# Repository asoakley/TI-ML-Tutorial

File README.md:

# TI-ML-Tutorial
<html>
<body>
<h1>TI Machine Learning Robotics</h1>
<h3>Tutorial repository for TI-RSLK MAX Machine Learning used for NC State ECE Senior Design Fall 2021-Spring 2022</h3>
<ul>
    <li>PCB folder contains Eagle CAD files for the custom PCB schematic file as well as the board file. It also includes the necessary gerbers and libraries needed to recreate the custom sensors PCB</li>
    <ul>
        <li>Eagle Libraries contains the libraries needed to recreate our schematic and board</li>
        <li>PCB Gerbers are the gerber files that can be sent to a manufacturer for printing</li>
    </ul>
    <li>libraries folder contains the libraries used in Arduino IDE to get the MSP432 microcontroller and the RSLK MAX to function. 
    It also contains two pretrained Edge Impulse libraries that we have tested for both Terrrain Recognition and Keyword Recognition</li>
    <li>prediction folder contains the Arduino code for running edge impulse models. 
    It contains code for both Audio and Accelerometer Machine Learning as well as a template code for any sensors you would like to have.</li>
    <li>test and training folder contains Arduino code to sample accelerometer and/or audio data of the RSLK MAX</li>
</ul>
    
<p> Check out our Hackster.io pages for
<a href="https://www.hackster.io/nc-state-ece-design-team-3-fall-2021-spring-2022/ti-rslk-machine-learning-robotics-terrain-recognition-a90367">Terrain Recognition</a> and 
<a href="https://www.hackster.io/nc-state-ece-design-team-3-fall-2021-spring-2022/ti-rslk-machine-learning-robotics-keyword-recognition-d96755">Keyword Recognition</a>!
</p>
</body>
</html>

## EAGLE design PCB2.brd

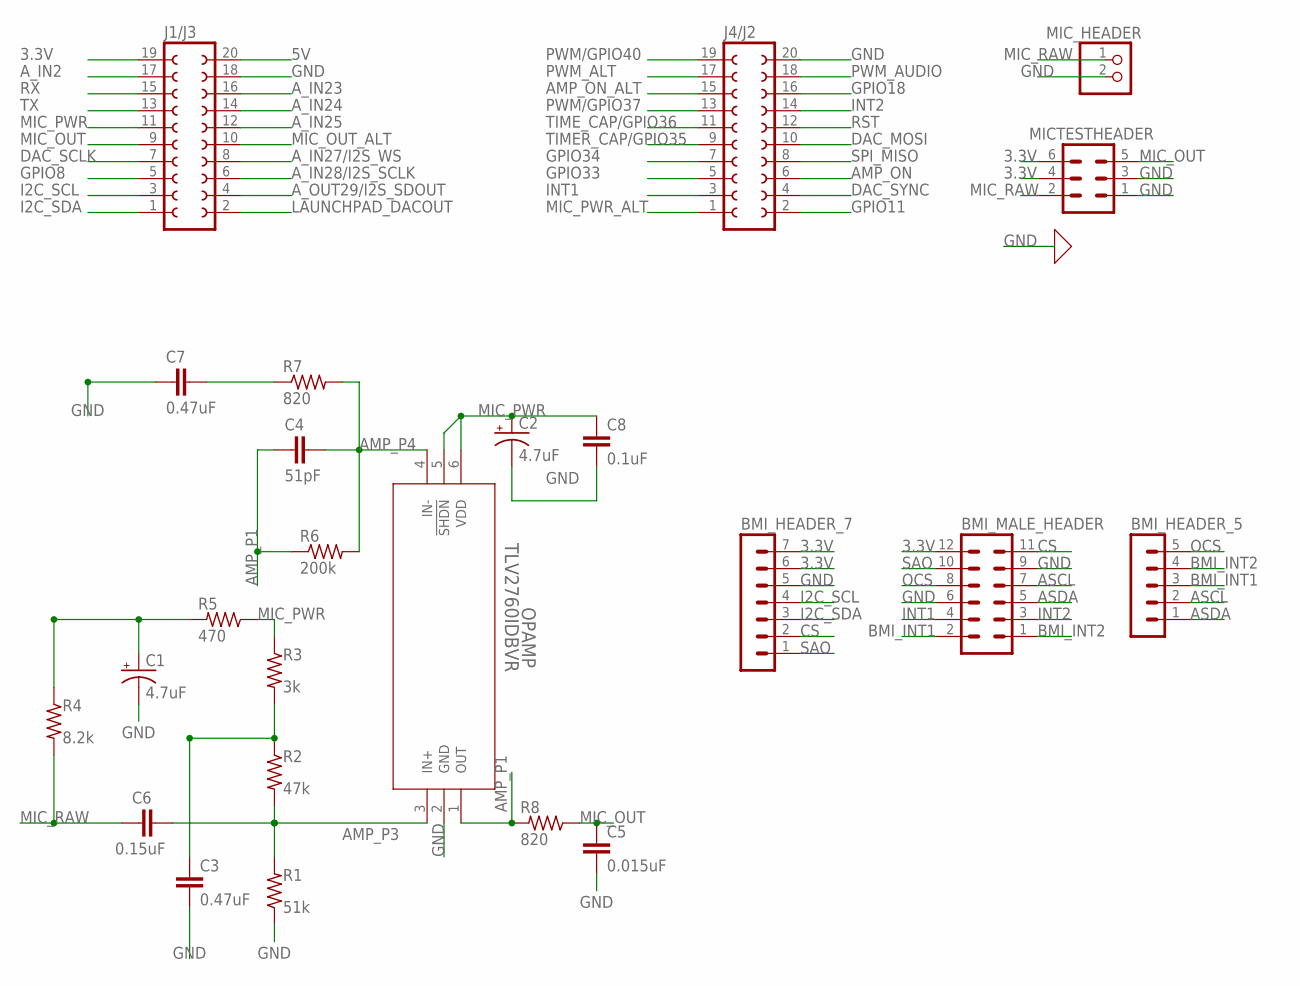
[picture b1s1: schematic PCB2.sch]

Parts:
BMI_HEADER_5: MA05-1
BMI_HEADER_7: MA07-1
BMI_MALE_HEADER: MA06-2
C1, C2: 4.7uF; B/3528-21W
C3, C7: 0.47uF; C0603
C4: 51pF; C0603
C5: 0.015uF; C0603
C6: 0.15uF; C0603
C8: 0.1uF; C0603
J1/J3, J4/J2: FE10-2W
MICTESTHEADER: MA03-2
MIC_HEADER: PINHD-1X2; 1X02
OPAMP: TLV2760IDBVR; DBV6
R1: 51k; MINI_MELF-0204R
R2: 47k; MINI_MELF-0204R
R3: 3k; MINI_MELF-0204R
R4: 8.2k; MINI_MELF-0204R
R5: 470; MINI_MELF-0204R
R6: 200k; MINI_MELF-0204R
R7, R8: 820; MINI_MELF-0204R

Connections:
3.3V: BMI_HEADER_7.6, BMI_HEADER_7.7, BMI_MALE_HEADER.12, J1/J3.19, MICTESTHEADER.4, MICTESTHEADER.6
5V: J1/J3.20
AMP_ON: J4/J2.6
AMP_ON_ALT: J4/J2.15
AMP_P1: C4.2, OPAMP.1 (OUT), R6.1, R8.2
AMP_P3: C6.2, OPAMP.3 (IN+), R1.2, R2.2
AMP_P4: C4.1, OPAMP.4 (IN-), R6.2, R7.2
ASCL: BMI_HEADER_5.2, BMI_MALE_HEADER.7
ASDA: BMI_HEADER_5.1, BMI_MALE_HEADER.5
A_IN2: J1/J3.17
A_IN23: J1/J3.16
A_IN24: J1/J3.14
A_IN25: J1/J3.12
A_IN27/I2S_WS: J1/J3.8
A_IN28/I2S_SCLK: J1/J3.6
A_OUT29/I2S_SDOUT: J1/J3.4
BMI_INT1: BMI_HEADER_5.3, BMI_MALE_HEADER.2
BMI_INT2: BMI_HEADER_5.4, BMI_MALE_HEADER.1
CS: BMI_HEADER_7.2, BMI_MALE_HEADER.11
DAC_MOSI: J4/J2.10
DAC_SCLK: J1/J3.7
DAC_SYNC: J4/J2.4
GND: BMI_HEADER_7.5, BMI_MALE_HEADER.6, BMI_MALE_HEADER.9, C1.-, C2.-, C3.2, C5.2, C7.2, C8.2, J1/J3.18, J4/J2.20, MICTESTHEADER.1, MICTESTHEADER.3, MIC_HEADER.2, OPAMP.2 (GND), R1.1
GPIO8: J1/J3.5
GPIO11: J4/J2.2
GPIO18: J4/J2.16
GPIO33: J4/J2.5
GPIO34: J4/J2.7
I2C_SCL: BMI_HEADER_7.4, J1/J3.3
I2C_SDA: BMI_HEADER_7.3, J1/J3.1
INT1: BMI_MALE_HEADER.4, J4/J2.3
INT2: BMI_MALE_HEADER.3, J4/J2.14
LAUNCHPAD_DACOUT: J1/J3.2
MIC_OUT: C5.1, J1/J3.9, MICTESTHEADER.5, R8.1
MIC_OUT_ALT: J1/J3.10
MIC_PWR: C2.+, C8.1, J1/J3.11, OPAMP.5 (!SHDN), OPAMP.6 (VDD), R3.1, R5.1
MIC_PWR_ALT: J4/J2.1
MIC_RAW: C6.1, MICTESTHEADER.2, MIC_HEADER.1, R4.2
unnamed: C3.1, R2.1, R3.2
unnamed: C1.+, R4.1, R5.2
unnamed: C7.1, R7.1
OCS: BMI_HEADER_5.5, BMI_MALE_HEADER.8
PWM/GPIO37: J4/J2.13
PWM/GPIO40: J4/J2.19
PWM_ALT: J4/J2.17
PWM_AUDIO: J4/J2.18
RST: J4/J2.12
RX: J1/J3.15
SAO: BMI_HEADER_7.1, BMI_MALE_HEADER.10
SPI_MISO: J4/J2.8
TIMER_CAP/GPIO35: J4/J2.9
TIME_CAP/GPIO36: J4/J2.11
TX: J1/J3.13

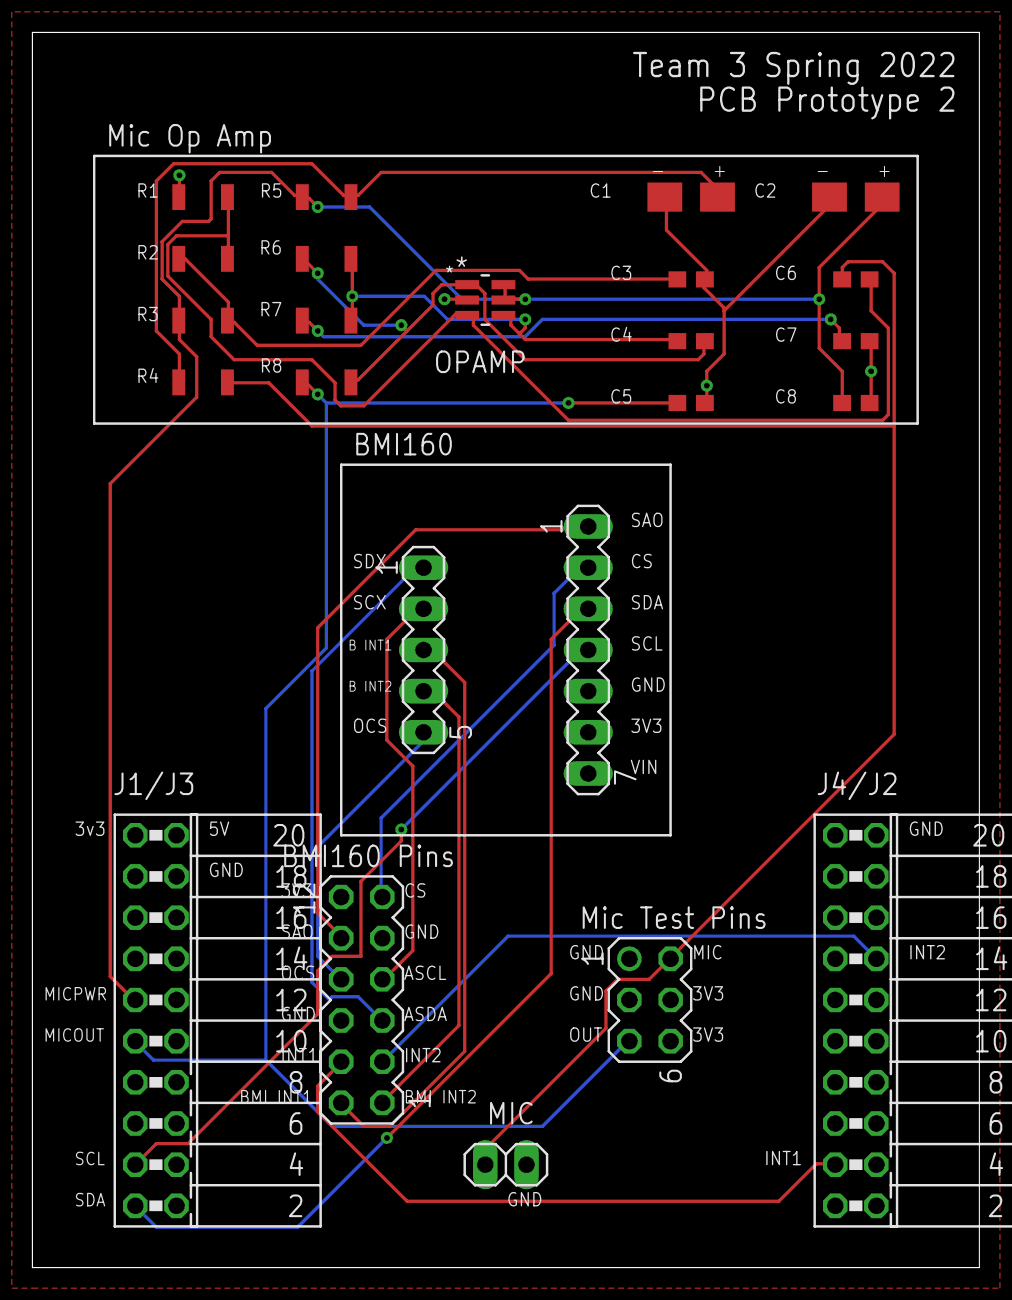
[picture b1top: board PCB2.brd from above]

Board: 2 copper layers, 58.4 x 76.2 mm, 24 parts (0 on the bottom side), 22 nets.

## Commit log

2022-04-19 Audio Sampling Code
2022-04-19 Accelerometer Sampling Code
2022-04-19 Sampling Code
2022-04-19 Predictions Code
2022-04-19 Device Support and Inferencing Libraries
2022-04-25 Template for creating your own prediction algorithm
2022-04-25 Fixed Comment
2022-04-25 Template for uploading sensor data to Edge Impulse
2022-04-25 Audio Inferencing Code
2022-04-25 Updated sampling rate
2022-04-25 Create BoM for custom PCB
2022-04-25 Rename PCB2.brd to PCB/PCB2.brd
2022-04-25 Rename PCB2.sch to PCB/PCB2.sch
2022-04-25 Rename PCB2.brd to PCB.brd
2022-04-25 Rename PCB2.sch to PCB.sch
2022-04-25 Rename PCB.brd to PCB2.brd
2022-04-25 Rename PCB.sch to PCB2.sch
2022-04-25 Pre-Trained Terrain Recognition Model
2022-04-25 Pre-Trained Audio Recognition Model
2022-04-25 Predict code
2022-04-25 Updated classes
2022-05-09 Updating Readme
    added hackster io links
